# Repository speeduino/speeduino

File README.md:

<div align="center">

##### A low cost, DIY friendly Engine Management System (ECU) based on the Arduino framework
</div>

## Speeduino
The Speeduino project is a flexible, fully featured Engine Management Systems (EMS aka ECU) based on the low cost and open source Arduino platform. It provides the hardware, firmware and software components that make up an engine management system, all provided under open licenses. With over 1000 installations, Speeduino has matured into a product that meets the needs of the hobbyist and enthusiast community without driving prices to the levels of traditional aftermarket ECUs.

## Documentation
The Speeduino online manual can be found at: https://wiki.speeduino.com

## Where to Buy
[Pre-made Speeduino units/boards are available from a number of official resellers](https://speeduino.com/home/where-to-buy)

These resellers all contribute a portion of sales back to the project to allow for continued development to take place and we encourage sales through them whenever possible. 
 
Of course, being open source, you are free to use the design files provided here to create your own hardware! 

## Support
In addition the manual referenced above, Speeduino has a large and very vibrant community of people to help out with your setup or any questions you might add. 

* [Discord](https://discord.gg/YWCEexaNDe)
* [Speeduino Forum](https://speeduino.com/forum) 
* [Facebook](https://www.facebook.com/groups/191918764521976/)

## Contributors

This project exists thanks to all the people who contribute, both in terms of code and testing provided. If you'd like to get involved, please have a read through [Contributing](contributing.md) and then jump on Discord to discuss things further

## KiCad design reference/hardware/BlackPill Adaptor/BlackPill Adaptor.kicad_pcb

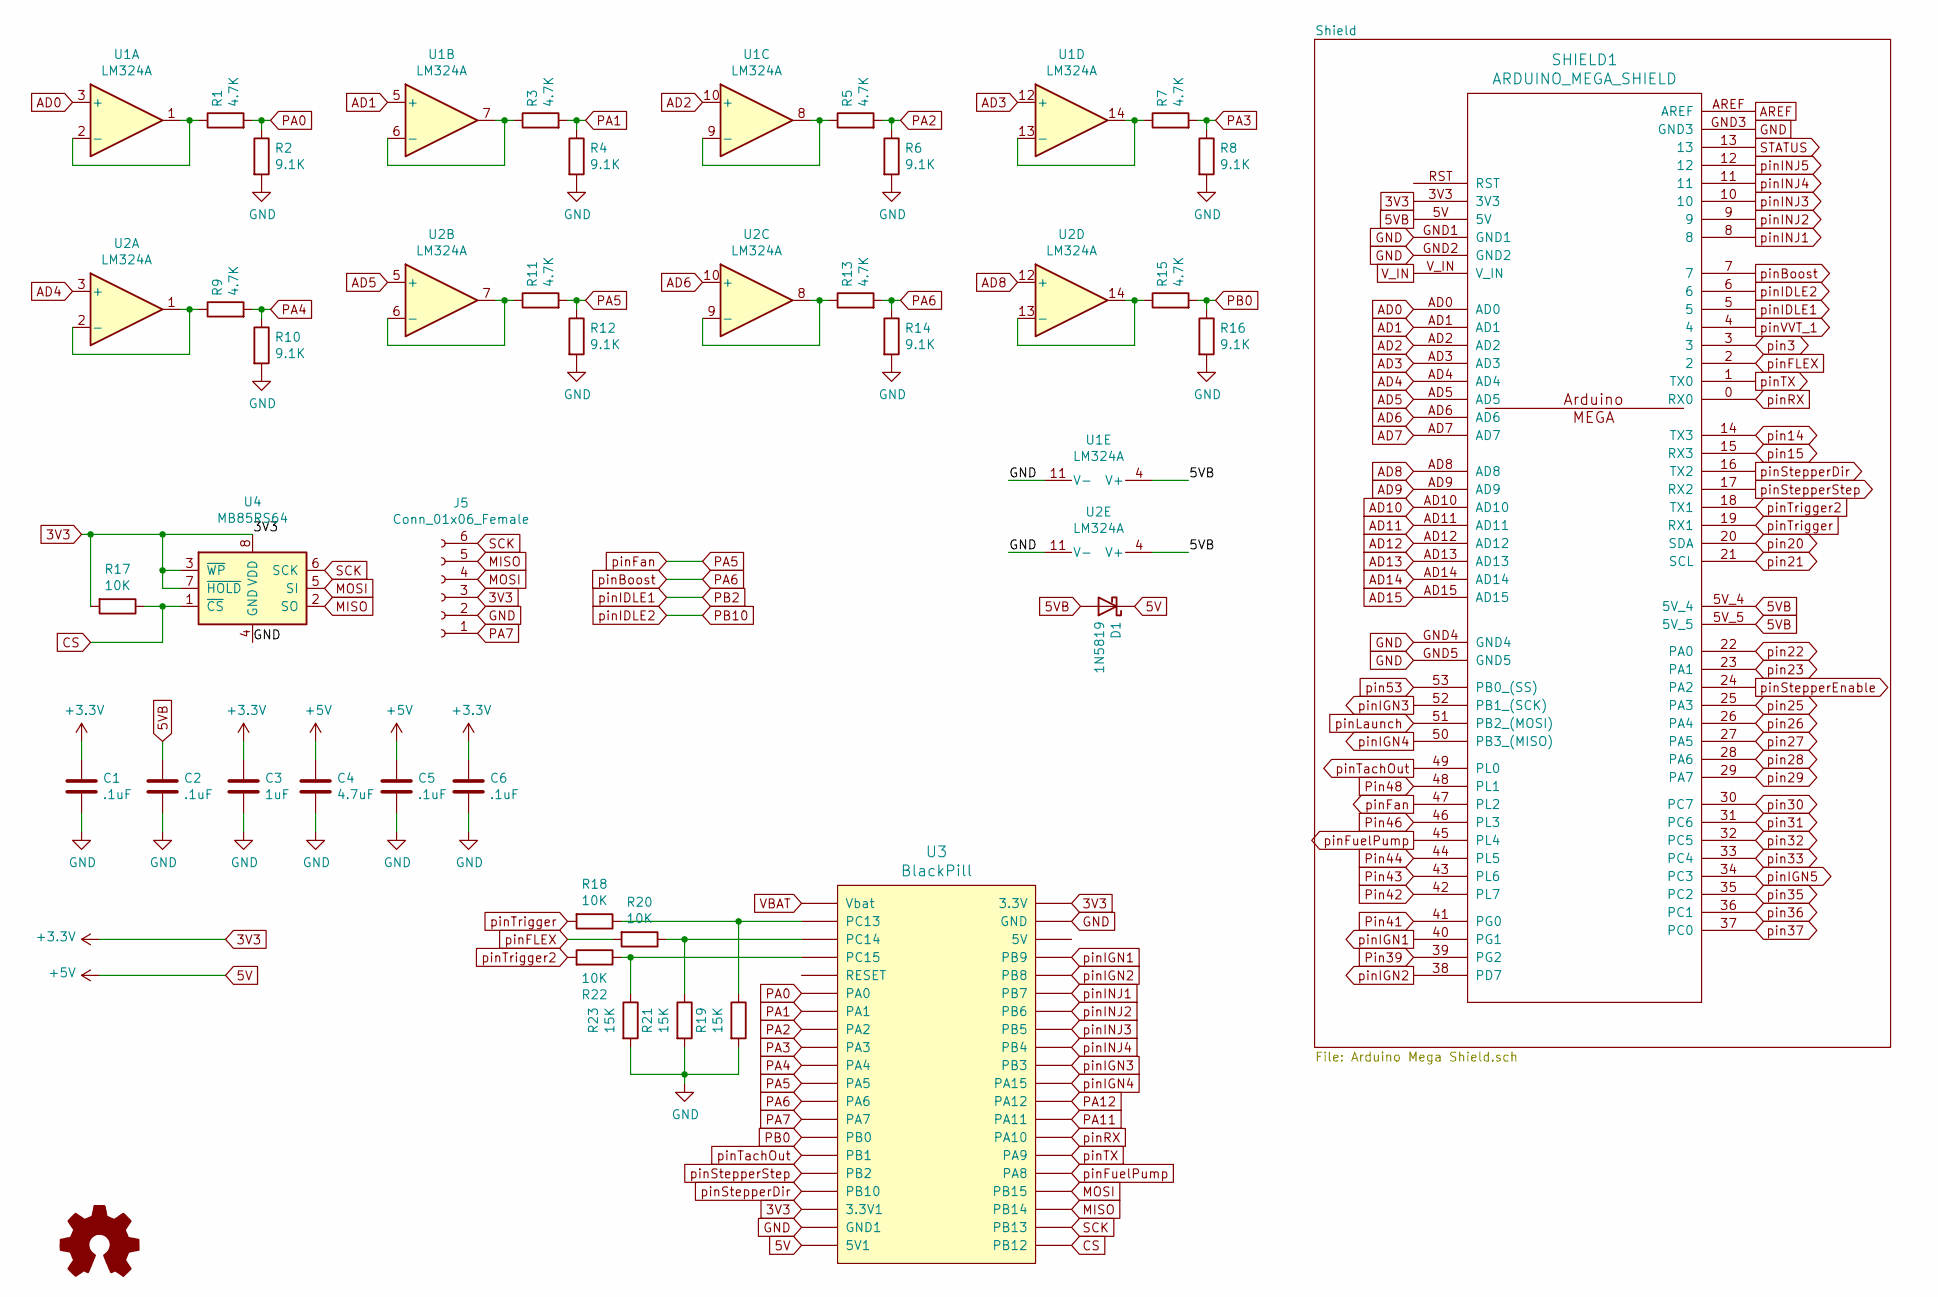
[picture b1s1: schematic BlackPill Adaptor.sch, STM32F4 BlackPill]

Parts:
C1, C2, C5, C6: .1uF; C_0805_2012Metric
C3: 1uF; C_1210_3225Metric
C4: 4.7uF; C_1210_3225Metric
D1: 1N5819; D_DO-41_SOD81_P10.16mm_Horizontal
J5: Conn_01x06_Female; PinHeader_1x06_P2.54mm_Vertical
R1, R3, R5, R7, R9, R11, R13, R15: 4.7K; R_0805_2012Metric
R2, R4, R6, R8, R10, R12, R14, R16: 9.1K; R_0805_2012Metric
R17, R18, R20, R22: 10K; R_0805_2012Metric
R19, R21, R23: 15K; R_0805_2012Metric
SHIELD1: ARDUINO_MEGA_SHIELD; ARDUINO MEGA SHIELD
U1: LM324A; SOIC-14_3.9x8.7mm_P1.27mm
U2: LM324A
U3: BlackPill; Maple_Mini
U4: MB85RS64; SOIC-8_5.23x5.23mm_P1.27mm

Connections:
3V3: C1.1, C3.1, C6.1, J5.3, R17.2, SHIELD1.3V3, U3.20 (3.3V), U3.38 (3.3V1), U4.3 (~WP), U4.7 (~HOLD), U4.8 (VDD)
5V: C4.1, C5.1, D1.1 (K), U3.40 (5V1)
5VB: C2.1, D1.2 (A), SHIELD1.5V, SHIELD1.5V_4, SHIELD1.5V_5, U1.4 (V+), U2.4 (V+)
AD0: SHIELD1.AD0, U1.3 (+)
AD1: SHIELD1.AD1, U1.5 (+)
AD2: SHIELD1.AD2, U1.10 (+)
AD3: SHIELD1.AD3, U1.12 (+)
AD4: SHIELD1.AD4, U2.3 (+)
AD5: SHIELD1.AD5, U2.5 (+)
AD6: SHIELD1.AD6, U2.10 (+)
AD7: SHIELD1.AD7
AD8: SHIELD1.AD8, U2.12 (+)
AD9: SHIELD1.AD9
AD10: SHIELD1.AD10
AD11: SHIELD1.AD11
AD12: SHIELD1.AD12
AD13: SHIELD1.AD13
AD14: SHIELD1.AD14
AD15: SHIELD1.AD15
AREF: SHIELD1.AREF
CS: R17.1, U3.1 (PB12), U4.1 (~CS)
GND: C1.2, C2.2, C3.2, C4.2, C5.2, C6.2, J5.2, R2.2, R4.2, R6.2, R8.2, R10.2, R12.2, R14.2, R16.2, R19.2, R21.2, R23.2, SHIELD1.GND1, SHIELD1.GND2, SHIELD1.GND3, SHIELD1.GND4, SHIELD1.GND5, U1.11 (V-), U2.11 (V-), U3.19 (GND), U3.39 (GND1), U4.4 (GND)
MISO: J5.5, U3.3 (PB14), U4.2 (SO)
MOSI: J5.4, U3.4 (PB15), U4.5 (SI)
unnamed: R1.1, U1.1, U1.2 (-)
unnamed: R3.1, U1.6 (-), U1.7
unnamed: R5.1, U1.8, U1.9 (-)
unnamed: R7.1, U1.13 (-), U1.14
unnamed: R9.1, U2.1, U2.2 (-)
unnamed: R11.1, U2.6 (-), U2.7
unnamed: R13.1, U2.8, U2.9 (-)
unnamed: R15.1, U2.13 (-), U2.14
unnamed: R18.1, R19.1, U3.22 (PC13)
unnamed: R20.1, R21.1, U3.23 (PC14)
unnamed: R22.1, R23.1, U3.24 (PC15)
PA0: R1.2, R2.1, U3.26 (PA0)
PA1: R3.2, R4.1, U3.27 (PA1)
PA2: R5.2, R6.1, U3.28 (PA2)
PA3: R7.2, R8.1, U3.29 (PA3)
PA4: R9.2, R10.1, U3.30 (PA4)
PA5: R11.2, R12.1, SHIELD1.47 (PL2), U3.31 (PA5)
PA6: R13.2, R14.1, SHIELD1.7, U3.32 (PA6)
PA7: J5.1, U3.33 (PA7)
PA11: U3.8 (PA11)
PA12: U3.9 (PA12)
PB0: R15.2, R16.1, U3.34 (PB0)
PB2: SHIELD1.5
PB10: SHIELD1.6
Pin39: SHIELD1.39 (PG2)
Pin41: SHIELD1.41 (PG0)
Pin42: SHIELD1.42 (PL7)
Pin43: SHIELD1.43 (PL6)
Pin44: SHIELD1.44 (PL5)
Pin46: SHIELD1.46 (PL3)
Pin48: SHIELD1.48 (PL1)
SCK: J5.6, U3.2 (PB13), U4.6 (SCK)
STATUS: SHIELD1.13
VBAT: U3.21 (Vbat)
V_IN: SHIELD1.V_IN
pin3: SHIELD1.3
pin14: SHIELD1.14 (TX3)
pin15: SHIELD1.15 (RX3)
pin20: SHIELD1.20 (SDA)
pin21: SHIELD1.21 (SCL)
pin22: SHIELD1.22 (PA0)
pin23: SHIELD1.23 (PA1)
pin25: SHIELD1.25 (PA3)
pin26: SHIELD1.26 (PA4)
pin27: SHIELD1.27 (PA5)
pin28: SHIELD1.28 (PA6)
pin29: SHIELD1.29 (PA7)
pin30: SHIELD1.30 (PC7)
pin31: SHIELD1.31 (PC6)
pin32: SHIELD1.32 (PC5)
pin33: SHIELD1.33 (PC4)
pin35: SHIELD1.35 (PC2)
pin36: SHIELD1.36 (PC1)
pin37: SHIELD1.37 (PC0)
pin53: SHIELD1.53 (PB0_(SS))
pinFLEX: R20.2, SHIELD1.2
pinFuelPump: SHIELD1.45 (PL4), U3.5 (PA8)
pinIGN1: SHIELD1.40 (PG1), U3.17 (PB9)
pinIGN2: SHIELD1.38 (PD7), U3.16 (PB8)
pinIGN3: SHIELD1.52 (PB1_(SCK)), U3.11 (PB3)
pinIGN4: SHIELD1.50 (PB3_(MISO)), U3.10 (PA15)
pinIGN5: SHIELD1.34 (PC3)
pinINJ1: SHIELD1.8, U3.15 (PB7)
pinINJ2: SHIELD1.9, U3.14 (PB6)
pinINJ3: SHIELD1.10, U3.13 (PB5)
pinINJ4: SHIELD1.11, U3.12 (PB4)
pinINJ5: SHIELD1.12
pinLaunch: SHIELD1.51 (PB2_(MOSI))
pinRX: SHIELD1.0 (RX0), U3.7 (PA10)
pinStepperDir: SHIELD1.16 (TX2), U3.37 (PB10)
pinStepperEnable: SHIELD1.24 (PA2)
pinStepperStep: SHIELD1.17 (RX2), U3.36 (PB2)
pinTX: SHIELD1.1 (TX0), U3.6 (PA9)
pinTachOut: SHIELD1.49 (PL0), U3.35 (PB1)
pinTrigger: R18.2, SHIELD1.19 (RX1)
pinTrigger2: R22.2, SHIELD1.18 (TX1)
pinVVT_1: SHIELD1.4

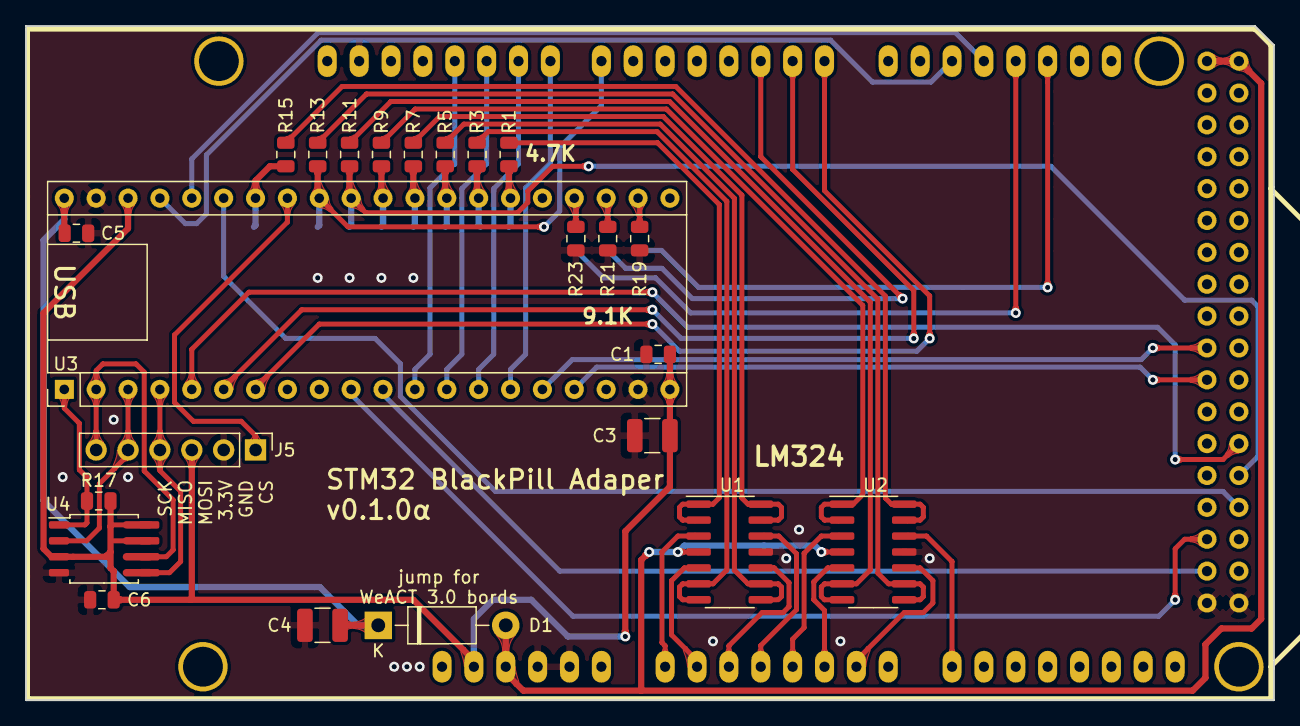
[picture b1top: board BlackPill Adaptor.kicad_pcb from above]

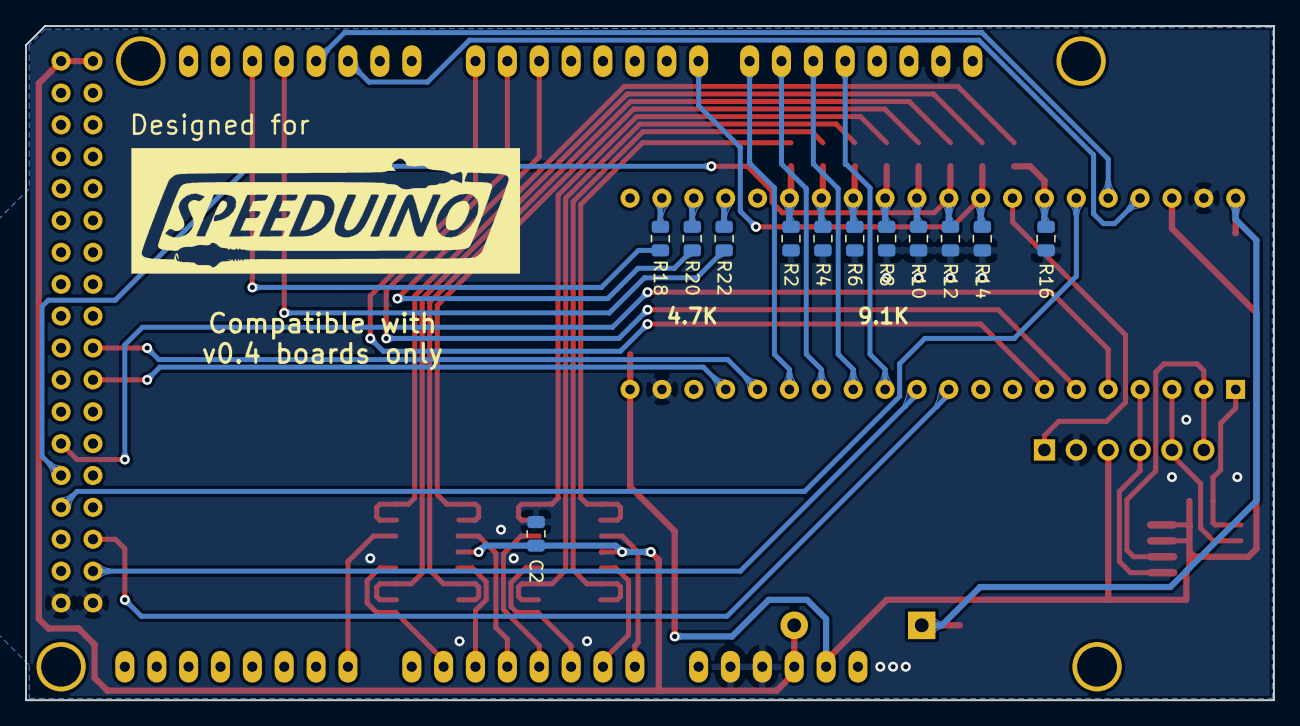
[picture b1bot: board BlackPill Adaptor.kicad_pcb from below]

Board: 2 copper layers, 99.4 x 53.7 mm, 36 parts (12 on the bottom side), 53 nets.

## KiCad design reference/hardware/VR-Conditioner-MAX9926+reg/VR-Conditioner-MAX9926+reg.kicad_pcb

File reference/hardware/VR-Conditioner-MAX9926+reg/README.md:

I hope this helps anyone interested.
Anyway, I've done what I can & it's now ready for many eye-balls.

Phill

2021-02-23
I have not made & tested this design but it is barely changed from the manufacrurers data sheets or other designs.
If you make & test it then please advise.

I'm new to KiCAD so I don't know how to do some things.  Such as how to have an 8-pin set of holes without a 3D chip sitting in it.
Or how to do an 8-pin header in the shape & pin count order of a chip.

2021-02-24
Changed version number to 3.5 so that it reflects relative cronology from previous design.
Renamed this from Notes.txt to README.md & corrected the date above.
Added Comments to schematic, inc. single-sided design allowing 'Letter' postage!
Updated BOM in schematic to reflect readily available parts found on OctoPart.

2021-04-22
Goal: give the left 6 passive components some space from the edge.
Re-route COUT1 from DIP.8 to SIL.4 in green so no signal traces are by the edge.
Shift right 5 components slightly right
Shift DIP, chip & hidden cap slightly right
Shift left 6 components slightly right
Re-route left 6 components to avoid side swapping, keeping the larger SMTs.
Ensure GNG plane encircles everything with a via in each corner.
Ensure all 'thin' traces are 0.20mm (up from 0.16)
Tidy with some symetry.

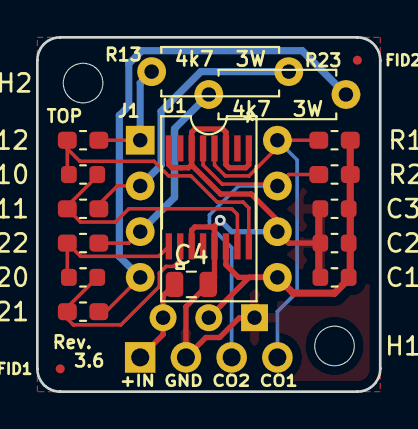
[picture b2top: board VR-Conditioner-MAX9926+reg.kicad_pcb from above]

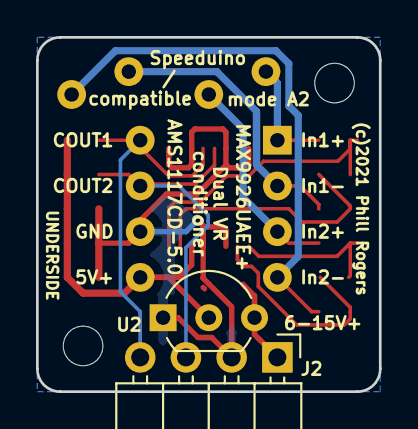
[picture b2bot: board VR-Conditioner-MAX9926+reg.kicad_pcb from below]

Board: 2 copper layers, 19.1 x 19.7 mm, 22 parts (2 on the bottom side), 13 nets.

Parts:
C1: 10n; C_0603_1608Metric
C2: 100n; C_0603_1608Metric
C3: 1u; C_0603_1608Metric
C4: 10u; C_0805_2012Metric
C10, C20: 1n; C_0603_1608Metric
FID1, FID2: Fiducial; Fiducial_0.5mm_Mask1mm
H1, H2: MountingHole; MountingHole_2.2mm_M2
J1: 8-pin header; DIP-8_W7.62mm
J2: Edge; PinHeader_1x04_P2.54mm_Horizontal
R10, R20: 1k; R_0603_1608Metric_Pad1.05x0.95mm_HandSolder
R11, R12, R21, R22: 10k; R_0603_1608Metric_Pad1.05x0.95mm_HandSolder
R13, R23: 4.7k; R_Axial_DIN0207_L6.3mm_D2.5mm_P7.62mm_Horizontal
U1: MAX9926UAEE+; MAX9926UAEE&plus_
U2: AMS1117CD-5.0; TO-92_Inline_Wide

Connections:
+12V: C4.1, J2.1, U2.3
/COUT1: J1.8, J2.4, R10.2, U1.4
/COUT2: J1.7, J2.3, R20.2, U1.5
GND: C1.2, C2.2, C3.2, C4.2, J1.6, J2.2, U1.1, U1.3, U1.6, U1.8, U1.11, U1.13, U2.1
unnamed: C10.1, R12.1, U1.16
unnamed: C10.2, R11.1, U1.15
unnamed: C20.1, R21.2, U1.10
unnamed: C20.2, R22.1, U1.9
unnamed: J1.1, R12.2, R13.1
unnamed: J1.2, R11.2, R13.2
unnamed: J1.3, R22.2, R23.1
unnamed: J1.4, R21.1, R23.2
VCC: C1.1, C2.1, C3.1, J1.5, R10.1, R20.1, U1.14, U2.2

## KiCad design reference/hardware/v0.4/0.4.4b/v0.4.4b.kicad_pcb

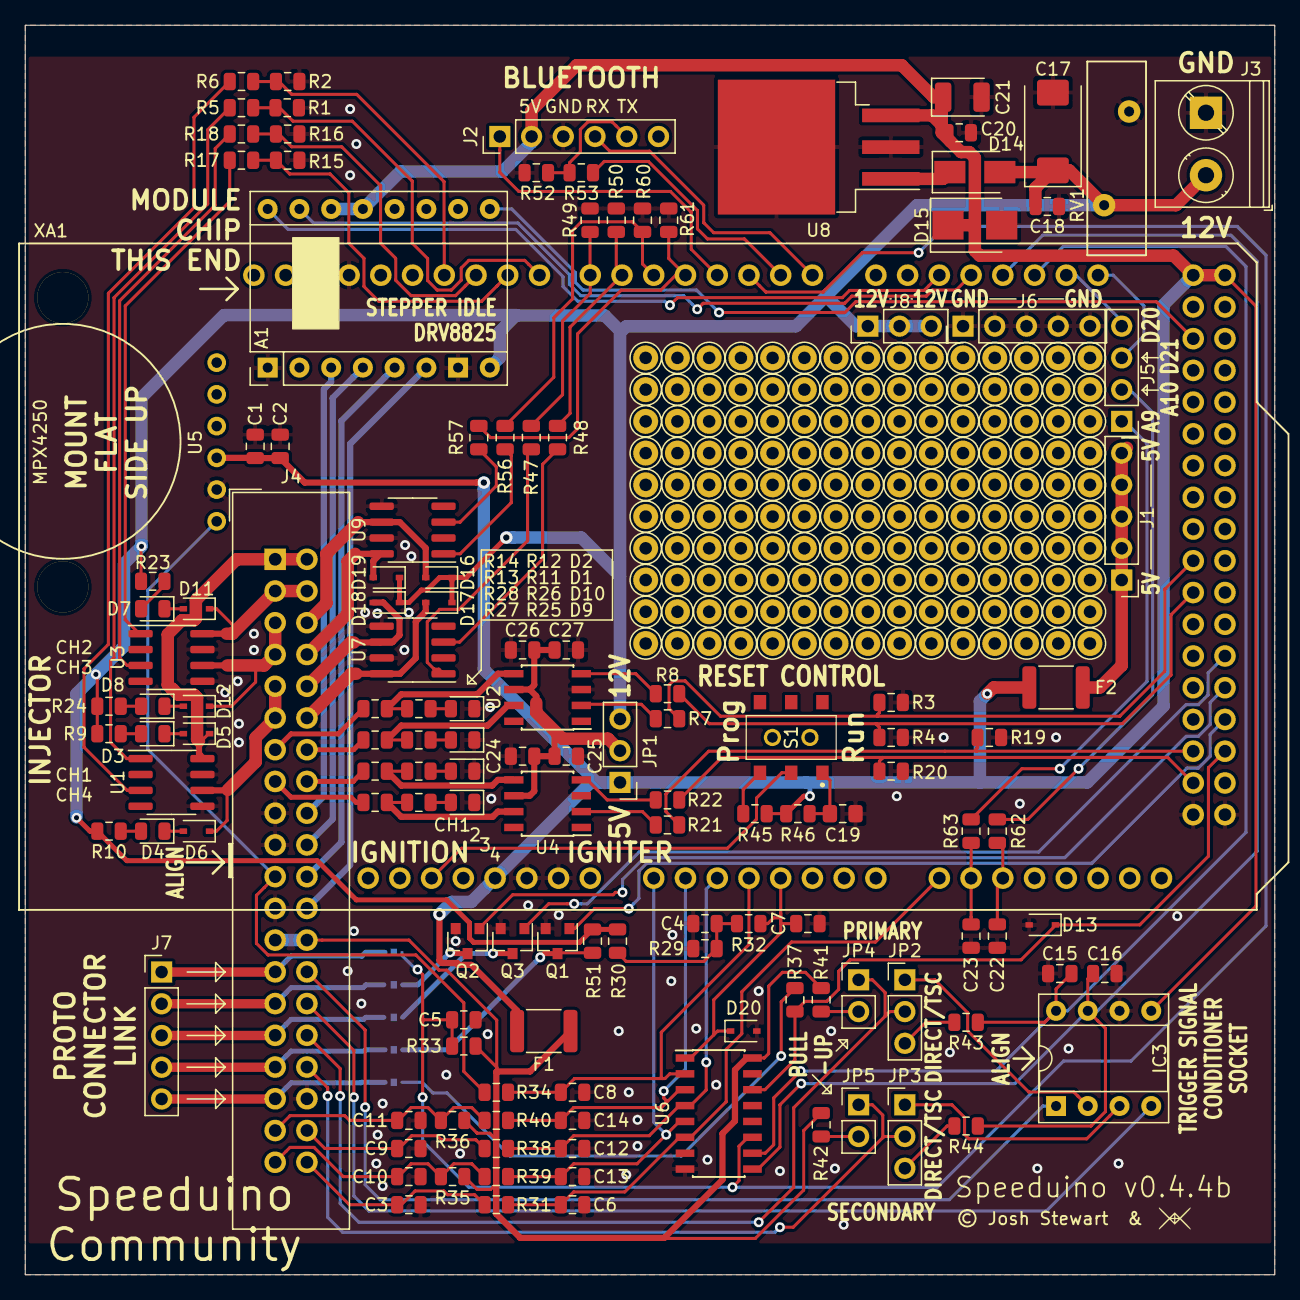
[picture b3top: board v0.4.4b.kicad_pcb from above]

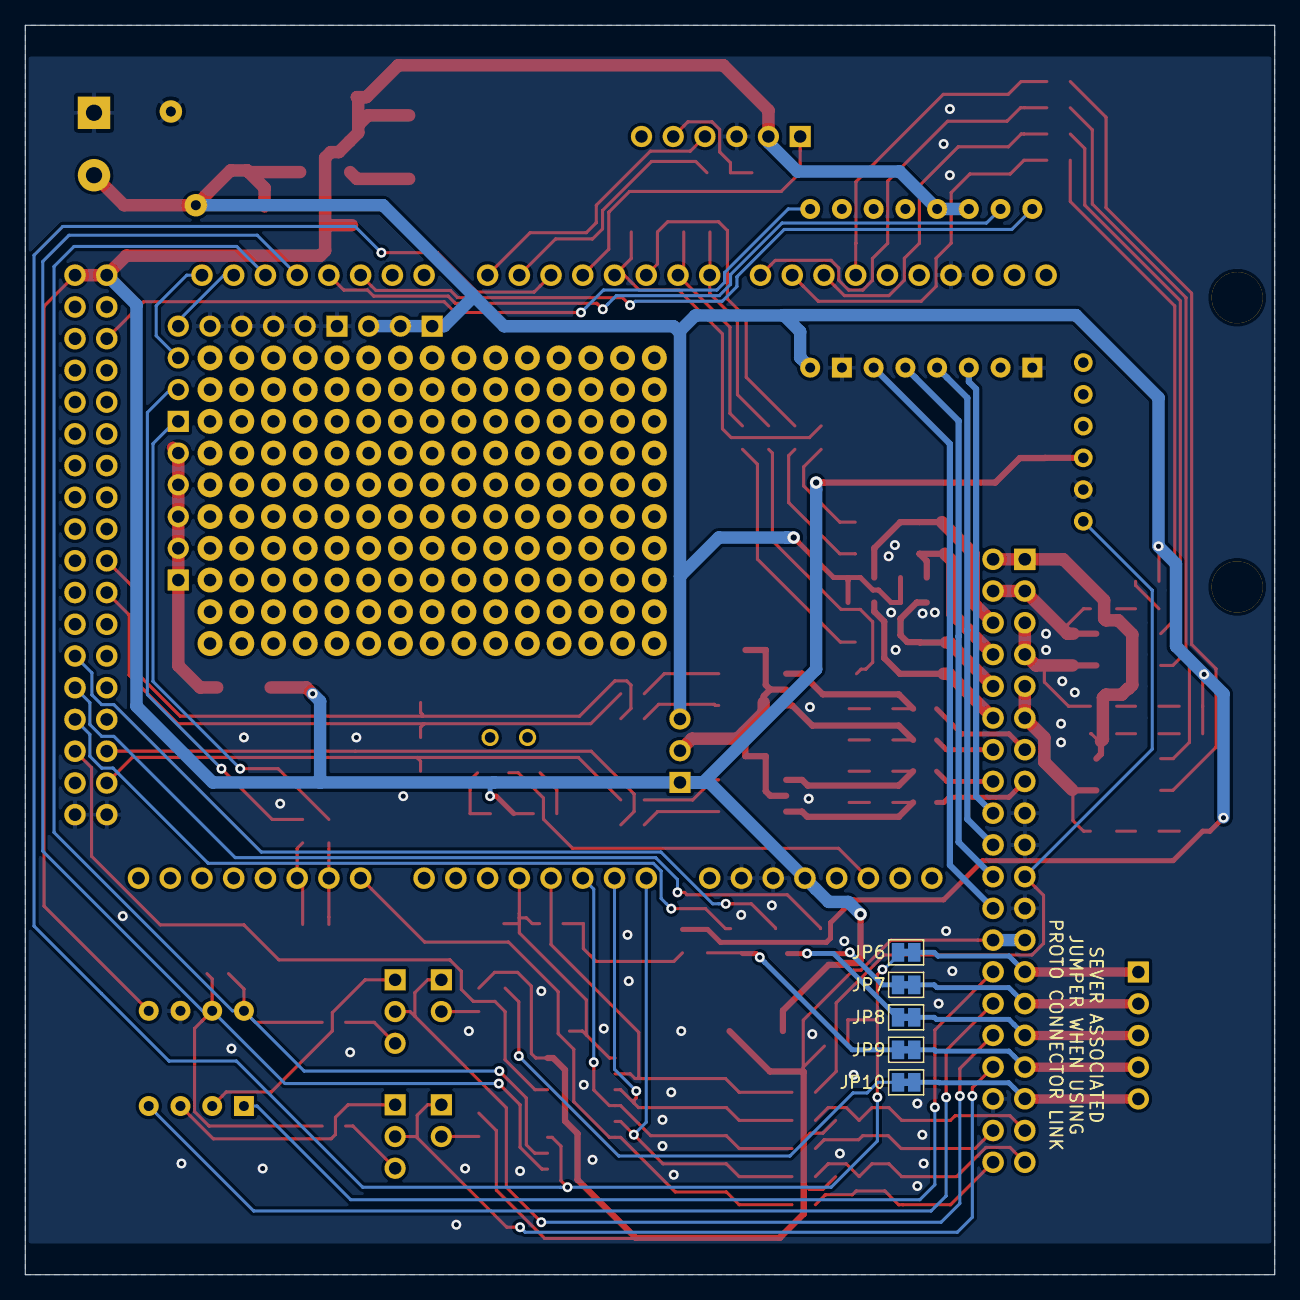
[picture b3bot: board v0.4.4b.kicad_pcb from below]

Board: 2 copper layers, 100.0 x 100.0 mm, 143 parts (5 on the bottom side), 117 nets.

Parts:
A1: Pololu_Breakout_DRV8825; Pololu_Breakout-16_15.2x20.3mm
C1, C15: 0.01uF; C_0805_2012Metric
C2, C25, C27: 1uF; C_0805_2012Metric
C3, C4, C9, C10, C11, C16, C18, C20, C22, C23, C24, C26: 0.1uF; C_0805_2012Metric
C5: 270nF; C_0805_2012Metric
C6, C7, C12, C13, C14: 0.22uF; C_0805_2012Metric
C8: 470pf; C_0805_2012Metric
C17: 10uF; CP_EIA-7343-31_Kemet-D
C19: 22uF; C_0805_2012Metric_Pad1.15x1.40mm_HandSolder
C21: 47uF; CP_EIA-3528-21_Kemet-B
D1, D2, D3, D4, D7, D8, D9, D10: LED; LED_0805_2012Metric
D5, D6, D11, D12, D16, D17, D18, D19: D; D_SOD-323
D13, D20: D_Zener; D_SOD-323
D14: B130-13-F; D_SMA
D15: 1SMB5919BT3G; D_SMB
F1, F2: Polyfuse; Fuse_1812_4532Metric
IC3: Trig Cond Socket; DIP-8_W7.62mm_Socket
J1, J6, J7: Conn_01x05; PinHeader_1x05_P2.54mm_Vertical
J2: Conn_01x06; PinHeader_1x06_P2.54mm_Vertical
J3: Conn_01x02; TerminalBlock_Phoenix_PT-1,5-2-5.0-H_1x02_P5.00mm_Horizontal
J4: Conn_02x20_Counter_Clockwise; IDC-Header_2x20_P2.54mm_Vertical
J5: Conn_01x04; PinHeader_1x04_P2.54mm_Vertical
J8: Conn_01x03; PinHeader_1x03_P2.54mm_Vertical
JP1: Ignition Voltage; PinHeader_1x03_P2.54mm_Vertical
JP2, JP3: VR-HALL; PinHeader_1x03_P2.54mm_Vertical
JP4, JP5: PULL-UP; PinHeader_1x02_P2.54mm_Vertical
JP6, JP7, JP8, JP9, JP10: SolderJumper_2_Bridged; SolderJumper-2_P1.3mm_Bridged_Pad1.0x1.5mm
Q1, Q2, Q3: SSM3K357R; SOT-23
R1, R2, R3, R4, R15, R16, R19, R20, R49, R50, R60, R61: 100k; R_0805_2012Metric
R5, R6, R7, R8, R17, R18, R21, R22, R29, R37, R41, R42, R47, R48, R53, R56, R57: 1k; R_0805_2012Metric
R9, R10, R11, R12, R23, R24, R25, R26, R33: 2.4k; R_0805_2012Metric
R13, R14, R27, R28: 10R; R_0805_2012Metric
R30: 3.9k; R_0805_2012Metric
R31, R32, R34, R38, R39, R40, R62, R63: 470R; R_0805_2012Metric
R35, R36: 2.49k; R_0805_2012Metric
R43, R44: 220R; R_0805_2012Metric
R45, R51: 10k; R_0805_2012Metric
R46: 120R; R_0805_2012Metric
R52: 2k; R_0805_2012Metric
RV1: Varistor; RV_Disc_D15.5mm_W4.7mm_P7.5mm
S1: AYZ0202AGRLC
U1, U3, U7, U9: VNLD5090; SOIC-8_3.9x4.9mm_P1.27mm
U2, U4: TC4424A; SOIC-8_3.9x4.9mm_P1.27mm
U5: MPX4250
U6: SP720; SOIC-16_3.9x9.9mm_P1.27mm
U8: LM2940S-5.0/NOPB; TO-263-3_TabPin2
XA1: Arduino_Mega2560_Shield; Arduino_Mega2560_Shield_IO_Only

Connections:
12V-SW: A1.8, C17.1, C18.1, D14.2, D16.1, D17.1, D18.1, D19.1, J3.2, J8.1, J8.2, J8.3, JP1.3, R9.2, R10.2, R23.2, R24.2, R30.2, R51.2, RV1.1
ADC-Clamp-1: C7.1, D20.1, R32.1, U6.1, XA1.A4
ADC-Clamp-2: C8.2, R34.1, U6.2, XA1.A3
ADC-Clamp-3: C14.1, R40.1, U6.3, XA1.A1
ADC-Clamp-4: C12.1, R38.1, U6.4, XA1.A2
ADC-Clamp-5: C13.1, R39.1, U6.5, XA1.A0
ADC-Clamp-6: C6.1, R31.1, U6.6, XA1.A8
ADC-Clamp-8: C16.2, IC3.7, R44.1, U6.9, XA1.D18
ADC-Clamp-9: C15.2, IC3.8, R43.1, U6.10, XA1.D19
ADC-Clamp-10: C5.1, JP6.1, R33.2, U6.11, XA1.D2
ADC-Clamp-13: D13.1, R37.2, U6.14, XA1.D51
BOOST-OUT: D17.2, J4.12, U7.8
CAM-IN: J4.34, JP3.2, JP5.1
CLT_Sensor: C11.1, J4.37, R36.1, R40.2
CRANK-IN: J4.32, JP2.2, JP4.1
Clutch_in: JP10.1, R37.1
FAN-OUT: JP7.1, Q2.3
FUELPUMP-OUT: JP8.1, Q3.3
GND: A1.1, A1.7, C1.1, C2.1, C3.2, C4.2, C5.2, C6.2, C7.2, C8.1, C9.2, C10.2, C11.2, C12.2, C13.2, C14.2, C15.1, C16.1, C17.2, C18.2, C19.2, C20.2, C21.2, C22.2, C23.2, C24.1, C25.1, C26.1, C27.1, D1.1, D2.1, D9.1, D10.1, D13.2, D15.2, D20.2, IC3.6, J2.3, J3.1, J4.17, J4.19, J4.23, J4.36, J6.1, J6.2, J6.3, J6.4, J6.5, Q1.2, Q2.2, Q3.2, R1.2, R2.1, R3.2, R4.1, R15.2, R16.1, R19.2, R20.1, R29.1, R49.2, R50.1, R52.2, R60.2, R61.1, RV1.2, U1.5, U1.7, U2.3, U3.5, U3.7, U4.3, U5.2, U6.8, U7.5, U7.7, U8.2, U9.5, U9.7, XA1.GND1, XA1.GND2, XA1.GND3, XA1.GND5, XA1.GND6
HC-1-OUT: D18.2, J4.10, U7.6
HC-2-OUT: D16.2, J4.6, U9.6
IAT_Sensor: C10.1, J4.39, R35.1, R39.2
IDLE-OUT: D19.2, J4.8, U9.8
IGN-1-OUT: J4.13, R14.1
IGN-2-OUT: J4.14, R13.1
IGN-3-OUT: J4.16, R28.1
IGN-4-OUT: J4.15, R27.1
INJ-1-OUT: D5.1, J4.1, J4.2, U1.8
INJ-2-OUT: D11.1, J4.3, J4.4, U3.8
INJ-3-OUT: D12.1, J4.5, J4.7, U3.6
INJ-4-OUT: D6.1, J4.9, J4.11, U1.6
MAP-EXT: J4.21, R34.2, U5.1
MCU-A9: C23.1, R63.1, XA1.A9
MCU-A10: C22.1, R62.2, XA1.A10
MCU-D0: J2.4, XA1.D0
MCU-D1: R53.1, XA1.D1
MCU-D3: J2.1, XA1.D3
MCU-D4: R57.2, R61.2, XA1.D4
MCU-D5: R56.2, R60.1, XA1.D5
MCU-D6: R48.2, R50.2, XA1.D6
MCU-D7: R47.2, R49.1, XA1.D7
MCU-D8: R1.1, R5.2, XA1.D8
MCU-D9: R15.1, R17.2, XA1.D9
MCU-D10: R16.2, R18.2, XA1.D10
MCU-D11: R2.2, R6.2, XA1.D11
MCU-D16: A1.16, XA1.D16
MCU-D17: A1.15, XA1.D17
MCU-D20: J5.4, XA1.D20
MCU-D21: J5.3, XA1.D21
MCU-D24: A1.9, XA1.D24
MCU-D38: R3.1, R7.2, XA1.D38
MCU-D40: R4.2, R8.2, XA1.D40
MCU-D45: Q3.1, XA1.D45
MCU-D47: Q2.1, XA1.D47
MCU-D49: Q1.1, XA1.D49
MCU-D50: R19.1, R21.2, XA1.D50
MCU-D52: R20.2, R22.2, XA1.D52
unnamed: C4.1, R29.2, R30.1, R32.2
unnamed: C19.1, R46.1, S1.1
unnamed: D1.2, R11.2
unnamed: D2.2, R12.2
unnamed: D3.1, D5.2
unnamed: D3.2, R9.1
unnamed: D4.1, D6.2
unnamed: D4.2, R10.1
unnamed: D7.2, R23.1
unnamed: D8.2, R24.1
unnamed: D9.2, R25.2
unnamed: D10.2, R26.2
unnamed: D7.1, D11.2
unnamed: D8.1, D12.2
unnamed: F2.2, J1.1, J1.2, J1.3, J1.4, J1.5
unnamed: IC3.2, JP2.1
unnamed: IC3.3, JP3.1
unnamed: J2.5, R52.1, R53.2
unnamed: J5.1, R63.2
unnamed: J5.2, R62.1
unnamed: JP2.3, R43.2
unnamed: JP3.3, R44.2
unnamed: JP4.2, R41.1
unnamed: JP5.2, R42.1
unnamed: R5.1, U1.1
unnamed: R6.1, U1.3
unnamed: R7.1, U2.2
unnamed: R8.1, U2.4
unnamed: R11.1, R13.2, U2.7
unnamed: R12.1, R14.2, U2.5
unnamed: R17.1, U3.1
unnamed: R18.1, U3.3
unnamed: R21.1, U4.2
unnamed: R22.1, U4.4
unnamed: R25.1, R27.2, U4.7
unnamed: R26.1, R28.2, U4.5
unnamed: R45.1, S1.3
unnamed: R47.1, U7.1
unnamed: R48.1, U7.3
unnamed: R56.1, U9.1
unnamed: R57.1, U9.3
O2_Sensor: C3.1, J4.40, R31.2
PROTO-1: J4.27, J7.1, JP6.2
PROTO-2: J4.29, J7.2, JP7.2
PROTO-3: J4.31, J7.3, JP8.2
PROTO-4: J4.33, J7.4, JP9.2
PROTO-5: J4.35, J7.5, JP10.2
RESET: S1.2, XA1.RST1
STEP-A1: A1.4, J4.20
STEP-A2: A1.3, J4.18
STEP-B1: A1.5, J4.22
STEP-B2: A1.6, J4.24
TACHO-OUT: JP9.1, Q1.3, R51.1
TPS_Sensor: C9.1, J4.38, R38.2
VDD: A1.13, A1.14, C1.2, C2.2, C20.1, C21.1, D15.1, F1.2, F2.1, IC3.5, J2.2, JP1.1, R45.2, R46.2, U5.3, U8.3, XA1.5V1, XA1.5V3, XA1.5V4
VDDA: F1.1, J4.25, J4.26, R33.1, R35.2, R36.2, R41.2, R42.2, U6.16
VR1-: IC3.1, J4.28
VR2-: IC3.4, J4.30
VRegIn: D14.1, U8.1
Vdrive: C24.2, C25.2, C26.2, C27.2, JP1.2, U2.6, U4.6

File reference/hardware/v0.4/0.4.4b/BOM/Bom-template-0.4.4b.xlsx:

Ref | Value | Footprint | Manufacture | Manufacture Part Number | Quantity | Specification | Pads/Pins
C1,C15 | 0.01uF | Capacitor_SMD:C_0805_2012Metric | Yageo | CC0805KRX7R9BB103 | 2 | https://www.digikey.com/product-detail/en/yageo/CC0805KRX7R9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 | 4
C17 | 10uF | Capacitor_Tantalum_SMD:CP_EIA-7343-31_Kemet-D | Kemet | T491D106K050AT | 1 | https://www.digikey.com/product-detail/en/kemet/T491D106K050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 | 2
C19 | 22uF | Capacitor_SMD:C_0805_2012Metric_Pad1.15x1.40mm_HandSolder | Samsung | CL21A226KQCLRNC | 1 | https://www.digikey.com.au/product-detail/en/samsung-electro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 | 2
C21 | 47uF | Capacitor_Tantalum_SMD:CP_EIA-3528-21_Kemet-B | AVX | TAJB476K006RNJ | 1 | https://www.digikey.com/product-detail/en/avx-corporation/TA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 | 2
C24,C26,C3,C9,C10,C11,C4,C16,C18,C20,C23,C22 | 0.1uF | Capacitor_SMD:C_0805_2012Metric | Yageo | CC0805KRX7R9BB104 | 12 | https://www.digikey.com.au/product-detail/en/yageo/CC0805KRX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 | 24
C25,C27,C2 | 1uF | Capacitor_SMD:C_0805_2012Metric | Yageo | CC0805KKX7R7BB105 | 3 | https://www.digikey.com/product-detail/en/yageo/CC0805KKX7R7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 | 6
C6,C12,C13,C14,C7,C5 | 0.22uF | Capacitor_SMD:C_0805_2012Metric | Samsung | CL21B224KOCNNNC | 6 | https://www.digikey.com/product-detail/en/samsung-electro-me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 | 12
C8 | 470pf | Capacitor_SMD:C_0805_2012Metric | Yageo | CC0805KRX7R9BB471 | 1 | https://www.digikey.com/product-detail/en/yageo/CC0805KRX7R9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 | 2
D12,D11,D5,D6,D18,D17,D19,D16 | D | Diode_SMD:D_SOD-323 | MCC | 1N4448WX-TP | 8 | https://www.digikey.com/product-detail/en/micro-commercial-c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 | 16
D13,D20 | D_Zener | Diode_SMD:D_SOD-323 | On Semi | MM3Z5V1ST1G | 2 | https://www.digikey.com/product-detail/en/on-semiconductor/M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 | 4
D14 | B130-13-F | Diode_SMD:D_SMA | Diodes,Inc | B130-13-F | 1 | https://www.digikey.com.au/product-detail/en/diodes-incorpor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 | 2
D15 | 1SMB5919BT3G | Diode_SMD:D_SMB | On Semi | 1SMB5919BT3G | 1 | https://www.digikey.com.au/product-detail/en/on-semiconducto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 | 2
D4,D3,D8,D7,D1,D2,D9,D10 | LED | LED_SMD:LED_0805_2012Metric | Osram | LH,R974-LP-1 | 8 | https://www.digikey.com/product-detail/en/osram-opto-semicon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 | 16
F1,F2 | Polyfuse | Fuse:Fuse_1812_4532Metric | Bel,Fuse | 0ZCC0050FF2C | 2 | https://www.digikey.com.au/product-detail/en/bel-fuse-inc/0Z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 | 4
JP1 | Ignition,Voltage | Connector_PinHeader_2.54mm:PinHeader_1x03_P2.54mm_Vertical | Harwin,Inc | M20-9990345 | 1 | https://www.digikey.com.au/products/en?keywords=M20-9990345 | 3
JP2,JP3 | VR-HALL | Connector_PinHeader_2.54mm:PinHeader_1x03_P2.54mm_Vertical | Harwin,Inc | M20-9990345 | 2 | https://www.digikey.com.au/products/en?keywords=M20-9990345 | 6
JP5,JP4 | PULL-UP | Connector_PinHeader_2.54mm:PinHeader_1x02_P2.54mm_Vertical | Harwin,Inc | M20-9990245, | 2 | https://www.digikey.com.au/products/en?keywords=M20-9990245 | 4
Q1,Q3,Q2 | SSM3K357R | Package_TO_SOT_SMD:SOT-23 | Toshiba | SSM3K357R | 3 | https://www.digikey.com.au/product-detail/en/toshiba-semicon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 | 6
R1,R2,R15,R16,R3,R4,R19,R20,R50,R49,R61,R60 | 100k | Resistor_SMD:R_0805_2012Metric | Yageo | RC0805FR-07100KL | 12 | https://www.digikey.com/product-detail/en/yageo/RC0805FR-071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 | 24
R10,R9,R24,R23,R11,R12,R25,R26,R33 | 2.4k | Resistor_SMD:R_0805_2012Metric | Yageo | RC0805FR-072K4L | 9 | https://www.digikey.com/product-detail/en/yageo/RC0805FR-072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 | 18
R13,R14,R27,R28 | 10R | Resistor_SMD:R_0805_2012Metric | Yageo | RC0805FR-0710RL | 4 | https://www.digikey.com/product-detail/en/yageo/RC0805FR-071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 | 8
R30 | 3.9k | Resistor_SMD:R_0805_2012Metric | Yageo | RC0805FR-073K9L | 1 | https://www.digikey.com/product-detail/en/yageo/RC0805FR-073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 | 2
R34,R31,R38,R39,R40,R32,R63,R62 | 470R | Resistor_SMD:R_0805_2012Metric | Panasonic | ERJ-6ENF4700V | 8 | https://www.digikey.com/product-detail/en/panasonic-electron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 | 16
R35,R36 | 2.49k | Resistor_SMD:R_0805_2012Metric | Yageo | RT0805BRD072K49L | 2 | https://www.digikey.com/product-detail/en/yageo/RT0805BRD072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 | 4
R43,R44 | 220R | Resistor_SMD:R_0805_2012Metric | Yageo | RC0805FR-07220RL | 2 | https://www.digikey.com/product-detail/en/yageo/RC0805FR-072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 | 4
R45,R51 | 10k | Resistor_SMD:R_0805_2012Metric | Yageo | RC0805JR-0710KL | 2 | https://www.digikey.com/product-detail/en/yageo/RC0805JR-071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 | 4
R46 | 120R | Resistor_SMD:R_0805_2012Metric | Yageo | RC0805FR-07120RL | 1 | https://www.digikey.com/product-detail/en/yageo/RC0805FR-071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 | 2
R5,R6,R17,R18,R7,R8,R21,R22,R29,R37,R41,R42,R47,R48,R56,R57,R53 | 1k | Resistor_SMD:R_0805_2012Metric | Yageo | RC0805FR-071KL | 17 | https://www.digikey.com/product-detail/en/yageo/RC0805FR-071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 | 34
R52 | 2k | Resistor_SMD:R_0805_2012Metric | Yageo | RC0805FR-072KL | 1 | https://www.digikey.com/product-detail/en/yageo/RC0805FR-072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 | 2
RV1 | Varistor | Varistor:RV_Disc_D15.5mm_W4.7mm_P7.5mm | Bournes,Inc | MOV-14D220K | 1 | https://www.digikey.com.au/product-detail/en/bourns-inc/MOV-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 | 2
S1 | AYZ0202AGRLC | Misc:AYZ0202AGRLC | C,&,K,COMPONENTS | AYZ0202AGRLC | 1 | https://www.digikey.com.au/product-detail/en/c-k/AYZ0202AGRL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 | 6
U1,U3,U7,U9 | VNLD5090 | Package_SO:SOIC-8_3.9x4.9mm_P1.27mm | STMicro | VNLD5090-E | 4 | https://www.digikey.com.au/products/en?keywords=VNLD5090-E | 32
U2,U4 | TC4424A | Package_SO:SOIC-8_3.9x4.9mm_P1.27mm | Microchip | TC4424AVOA | 2 | https://www.digikey.com/product-detail/en/microchip-technolo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 | 16
U5 | MPX4250 | Misc:MPX4250 | NXP | MPX4250AP | 1 | https://www.digikey.com.au/product-detail/en/nxp-usa-inc/MPX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 | 6
U6 | SP720 | Package_SO:SOIC-16_3.9x9.9mm_P1.27mm | Littelfuse | SP720ABTG | 1 | https://www.digikey.com/product-detail/en/littelfuse-inc/SP7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 | 16
U8 | LM2940S-5.0/NOPB | Package_TO_SOT_SMD:TO-263-3_TabPin2 | TI | LM2940S-5.0/NOPB | 1 | https://www.digikey.com.au/products/en?keywords=LM2940S-5.0%2FNOPB | 3

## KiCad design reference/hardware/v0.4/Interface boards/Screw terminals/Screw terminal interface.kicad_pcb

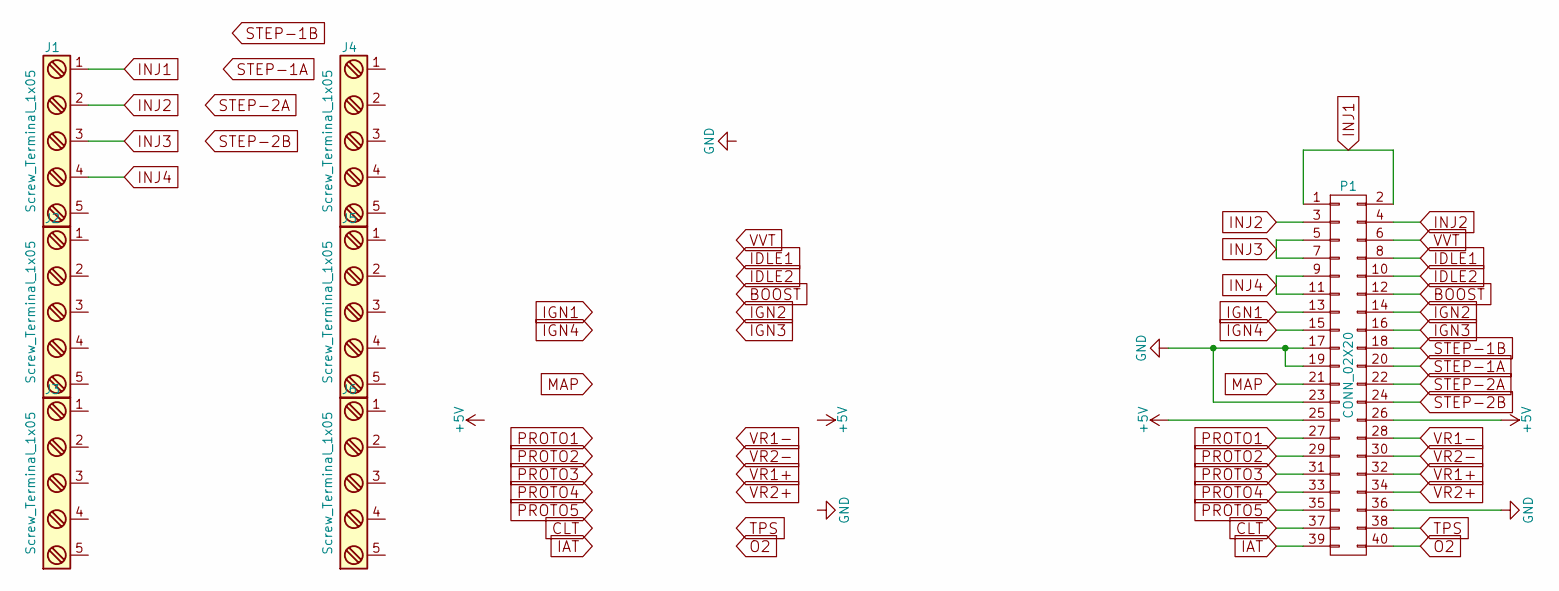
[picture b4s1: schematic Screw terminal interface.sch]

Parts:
J1, J2, J3, J4, J5, J6: Screw_Terminal_1x05; TerminalBlock_Phoenix_PT-1,5-5-5.0-H_1x05_P5.00mm_Horizontal
P1: CONN_02X20; IDC_Header_Straight_40pins

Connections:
+5V: P1.25, P1.26
BOOST: P1.12
CLT: P1.37
GND: P1.17, P1.19, P1.23, P1.36
IAT: P1.39
IDLE1: P1.8
IDLE2: P1.10
IGN1: P1.13
IGN2: P1.14
IGN3: P1.16
IGN4: P1.15
INJ1: J1.1, P1.1, P1.2
INJ2: J1.2, P1.3, P1.4
INJ3: J1.3, P1.5, P1.7
INJ4: J1.4, P1.9, P1.11
MAP: P1.21
O2: P1.40
PROTO1: P1.27
PROTO2: P1.29
PROTO3: P1.31
PROTO4: P1.33
PROTO5: P1.35
STEP-1A: P1.20
STEP-1B: P1.18
STEP-2A: P1.22
STEP-2B: P1.24
TPS: P1.38
VR1+: P1.32
VR1-: P1.28
VR2+: P1.34
VR2-: P1.30
VVT: P1.6

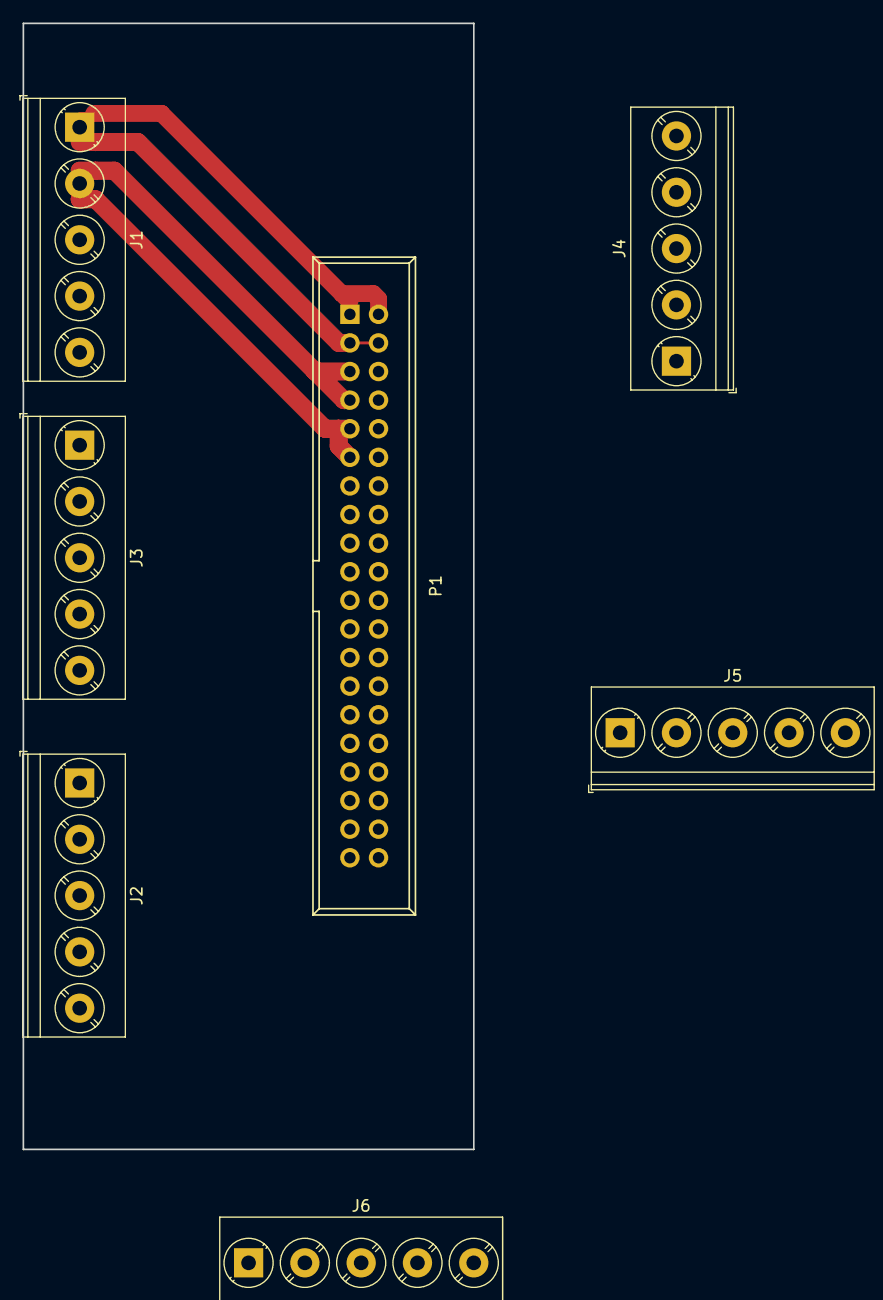
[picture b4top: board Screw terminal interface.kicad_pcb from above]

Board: 2 copper layers, 40.0 x 100.0 mm, 7 parts (0 on the bottom side), 6 nets.

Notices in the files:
README.md:
License: GPLv3
reference/hardware/VR-Conditioner-MAX9926+reg/VR-Conditioner-MAX9926+reg.kicad_pcb:
(c)2021 Phill Rogers @ TechColab.co.je
reference/hardware/v0.4/0.4.4b/v0.4.4b.kicad_pcb:
© Josh Stewart  &
parts and their libraries:
Copyright 2016 Accelerated Designs. All rights reserved.
